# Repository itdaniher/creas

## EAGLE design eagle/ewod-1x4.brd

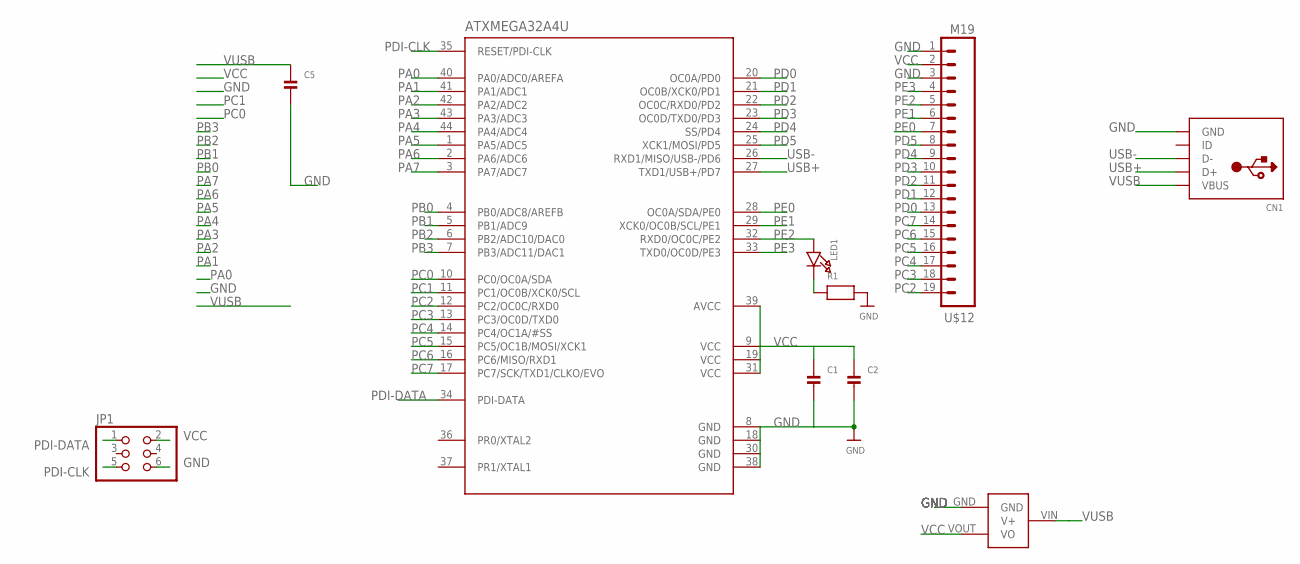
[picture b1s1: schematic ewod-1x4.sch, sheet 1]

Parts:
ATXMEGA32A4U: ATXMEGAXXA4U-AU; TQFP-44
C1, C2, C5: CAP_CERAMIC0603; 0603
CN1: USBMICROB; USB-MICROB
JP1: HEADER-2X3; 2X03
LED1: LED0603; CHIPLED_0603
R1: RESISTOR0603; 0603
U$10: MCP1700; SOT23-3
U$12: M19; 1X19

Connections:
GND: ATXMEGA32A4U.8 (GND), ATXMEGA32A4U.18 (GND), ATXMEGA32A4U.30 (GND), ATXMEGA32A4U.38 (GND), C1.2, C2.2, C5.2, CN1.P5 (GND), JP1.6, R1.2, U$10.GND, U$12.1, U$12.3; also elsewhere on the board
unnamed: LED1.C, R1.1
PA0: ATXMEGA32A4U.40 (PA0/ADC0/AREFA); also elsewhere on the board
PA1: ATXMEGA32A4U.41 (PA1/ADC1); also elsewhere on the board
PA2: ATXMEGA32A4U.42 (PA2/ADC2); also elsewhere on the board
PA3: ATXMEGA32A4U.43 (PA3/ADC3); also elsewhere on the board
PA4: ATXMEGA32A4U.44 (PA4/ADC4)
PA5: ATXMEGA32A4U.1 (PA5/ADC5)
PA6: ATXMEGA32A4U.2 (PA6/ADC6)
PA7: ATXMEGA32A4U.3 (PA7/ADC7)
PB0: ATXMEGA32A4U.4 (PB0/ADC8/AREFB)
PB1: ATXMEGA32A4U.5 (PB1/ADC9)
PB2: ATXMEGA32A4U.6 (PB2/ADC10/DAC0)
PB3: ATXMEGA32A4U.7 (PB3/ADC11/DAC1)
PC0: ATXMEGA32A4U.10 (PC0/OC0A/SDA)
PC1: ATXMEGA32A4U.11 (PC1/OC0B/XCK0/SCL)
PC2: ATXMEGA32A4U.12 (PC2/OC0C/RXD0), U$12.19
PC3: ATXMEGA32A4U.13 (PC3/OC0D/TXD0), U$12.18
PC4: ATXMEGA32A4U.14 (PC4/OC1A/#SS), U$12.17; also elsewhere on the board
PC5: ATXMEGA32A4U.15 (PC5/OC1B/MOSI/XCK1), U$12.16; also elsewhere on the board
PC6: ATXMEGA32A4U.16 (PC6/MISO/RXD1), U$12.15; also elsewhere on the board
PC7: ATXMEGA32A4U.17 (PC7/SCK/TXD1/CLKO/EVO), U$12.14; also elsewhere on the board
PD0: ATXMEGA32A4U.20 (OC0A/PD0), U$12.13
PD1: ATXMEGA32A4U.21 (OC0B/XCK0/PD1), U$12.12
PD2: ATXMEGA32A4U.22 (OC0C/RXD0/PD2), U$12.11
PD3: ATXMEGA32A4U.23 (OC0D/TXD0/PD3), U$12.10
PD4: ATXMEGA32A4U.24 (SS/PD4), U$12.9
PD5: ATXMEGA32A4U.25 (XCK1/MOSI/PD5), U$12.8
PDI-CLK: ATXMEGA32A4U.35 (RESET/PDI-CLK), JP1.5
PDI-DATA: ATXMEGA32A4U.34 (PDI-DATA), JP1.1
PE0: ATXMEGA32A4U.28 (OC0A/SDA/PE0), U$12.7
PE1: ATXMEGA32A4U.29 (XCK0/OC0B/SCL/PE1), U$12.6
PE2: ATXMEGA32A4U.32 (RXD0/OC0C/PE2), LED1.A, U$12.5
PE3: ATXMEGA32A4U.33 (TXD0/OC0D/PE3), U$12.4
USB+: ATXMEGA32A4U.27 (TXD1/USB+/PD7), CN1.P3 (D+)
USB-: ATXMEGA32A4U.26 (RXD1/MISO/USB-/PD6), CN1.P2 (D-)
VCC: ATXMEGA32A4U.9 (VCC), ATXMEGA32A4U.19 (VCC), ATXMEGA32A4U.31 (VCC), ATXMEGA32A4U.39 (AVCC), C1.1, C2.1, JP1.2, U$10.VOUT (VO), U$12.2
VUSB: C5.1, CN1.P1 (VBUS), U$10.VIN (V+)

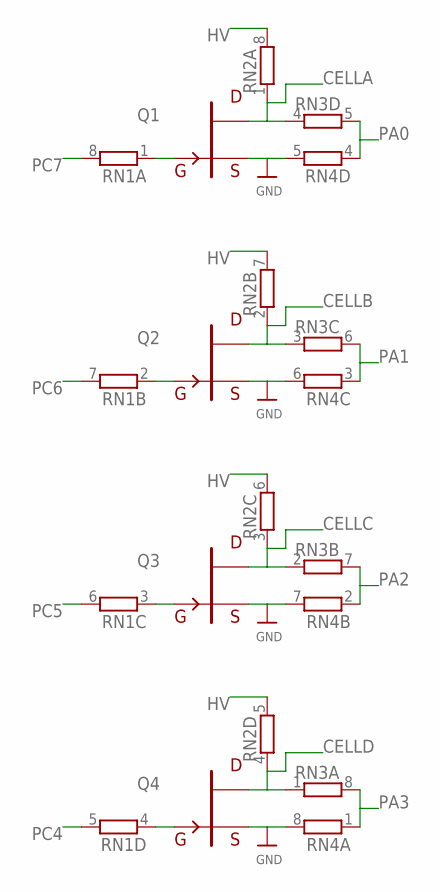
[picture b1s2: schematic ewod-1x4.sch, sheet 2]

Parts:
Q1, Q2, Q3, Q4: FET-N; SOT23
RN1, RN2, RN3, RN4: RNETWORK; RN8P-4R-CRA06S

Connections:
CELLA: Q1.3 (D), RN2.1, RN3.4 (1)
CELLB: Q2.3 (D), RN2.2 (1), RN3.3 (1)
CELLC: Q3.3 (D), RN2.3 (1), RN3.2 (1)
CELLD: Q4.3 (D), RN2.4 (1), RN3.1
GATEA: Q1.1 (G), RN1.1
GATEB: Q2.1 (G), RN1.2 (1)
GATEC: Q3.1 (G), RN1.3 (1)
GATED: Q4.1 (G), RN1.4 (1)
GND: Q1.2 (S), Q2.2 (S), Q3.2 (S), Q4.2 (S), RN4.5 (2), RN4.6 (2), RN4.7 (2), RN4.8 (2); also elsewhere on the board
HV: RN2.5 (2), RN2.6 (2), RN2.7 (2), RN2.8 (2); also elsewhere on the board
PA0: RN3.5 (2), RN4.4 (1); also elsewhere on the board
PA1: RN3.6 (2), RN4.3 (1); also elsewhere on the board
PA2: RN3.7 (2), RN4.2 (1); also elsewhere on the board
PA3: RN3.8 (2), RN4.1; also elsewhere on the board
PC4: RN1.5 (2); also elsewhere on the board
PC5: RN1.6 (2); also elsewhere on the board
PC6: RN1.7 (2); also elsewhere on the board
PC7: RN1.8 (2); also elsewhere on the board

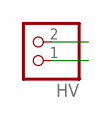
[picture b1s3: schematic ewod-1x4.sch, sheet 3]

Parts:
HV: HEADER-1X2ROUND; 1X02_ROUND

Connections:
GND: HV.2; also elsewhere on the board
HV: HV.1; also elsewhere on the board

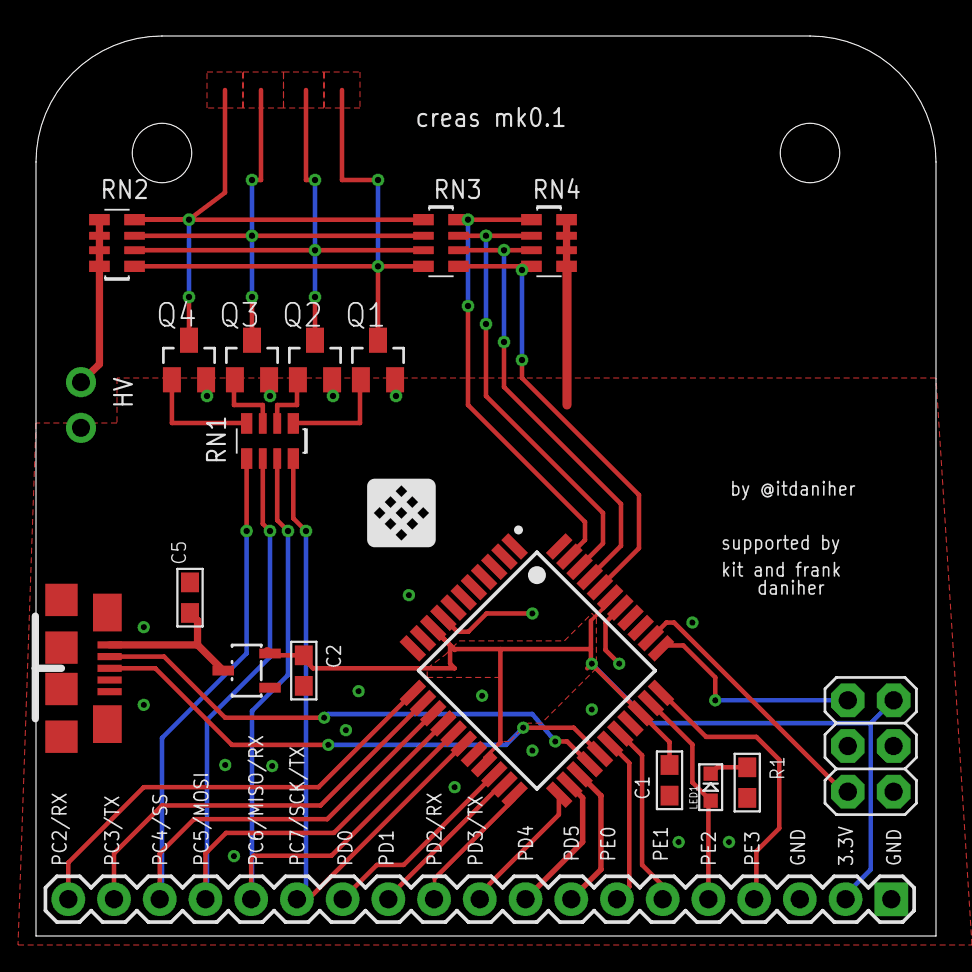
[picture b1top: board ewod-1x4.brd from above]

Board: 2 copper layers, 50.0 x 50.0 mm, 22 parts (0 on the bottom side), 37 nets.

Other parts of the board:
U$1, U$2: STAND-OFF
U$5: LOGO_NONOLITH

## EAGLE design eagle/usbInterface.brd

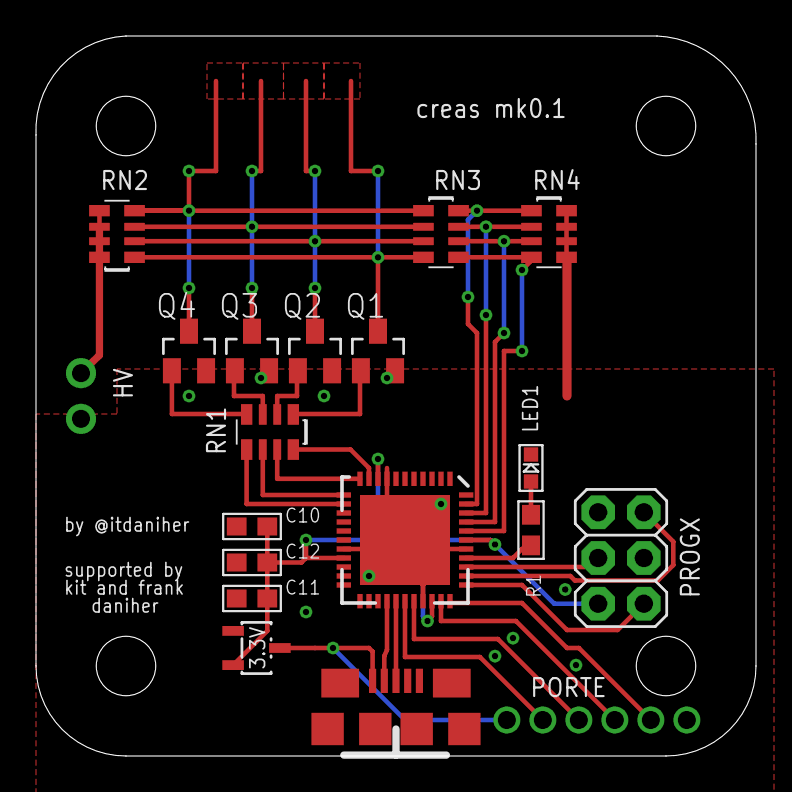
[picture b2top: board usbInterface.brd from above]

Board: 2 copper layers, 40.0 x 40.0 mm, 24 parts (1 on the bottom side), 31 nets.

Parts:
3.3V: VREG; SOT23-3
C10: 1uF; 0603
C11: .1uF; 0603
C12: .01uF; 0603
CN1: USB-MICROB
HV: 1X02_ROUND
LED1: CHIPLED_0603
PORTE: 1X06_ROUND_2MM
PROGX: 2X03
Q1, Q2, Q3, Q4: SOT23
R1: 120o; 0603
RN1, RN2, RN3, RN4: RN8P-4R-CRA06S
U$1, U$2, U$3, U$4: STAND-OFF
U$5: LOGO_NONOLITH
XM1: QFN-44

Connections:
3.3V: 3.3V.2, C10.2, C11.2, C12.2, PROGX.2, XM1.9, XM1.19, XM1.31, XM1.39
5V: 3.3V.3, CN1.P1, PORTE.1
ADCA: RN3.5, RN4.4, XM1.40
ADCB: RN3.6, RN4.3, XM1.41
ADCC: RN3.7, RN4.2, XM1.42
ADCD: RN3.8, RN4.1, XM1.43
BOOTLOAD: PROGX.4, XM1.36
CELLA: Q1.3, RN2.1, RN3.4
CELLB: Q2.3, RN2.2, RN3.3
CELLC: Q3.3, RN2.3, RN3.2
CELLD: Q4.3, RN2.4, RN3.1
GATEA: Q1.1, RN1.1
GATEB: Q2.1, RN1.2
GATEC: Q3.1, RN1.3
GATED: Q4.1, RN1.4
GND: 3.3V.1, C10.1, C11.1, C12.1, CN1.P5, HV.2, LED1.C, PORTE.6, PROGX.6, Q1.2, Q2.2, Q3.2, Q4.2, RN4.5, RN4.6, RN4.7, RN4.8, XM1.8, XM1.18, XM1.30, XM1.38
HV: HV.1, RN2.5, RN2.6, RN2.7, RN2.8
OC0A: RN1.8, XM1.10
OC0B: RN1.7, XM1.11
OC0C: RN1.6, XM1.12
OC0D: RN1.5, XM1.13
PDI-CLK: PROGX.5, XM1.35
PDI-DATA: PROGX.1, XM1.34
PE0: PORTE.2, XM1.28
PE1: PORTE.3, XM1.29
PE2: PORTE.4, XM1.32
PE3: PORTE.5, XM1.33
PR1: R1.1, XM1.37
PR1-P: LED1.A, R1.2
USB+: CN1.P3, XM1.27
USB-: CN1.P2, XM1.26

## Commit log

2012-07-11 initial commit of usbInterface board & schematic
2012-07-29 large amount of work on 1x4 ewod array
2012-07-29 rename usbInterface to be slightly more descriptive
2013-01-05 redo to 50x50mm
2013-01-05 final tweaks - fix drill width, add tenting, fix a few other things
2014-12-11 bulk commit of interesting things

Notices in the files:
eagle/ewod-1x4.brd:
CC-By-SA
